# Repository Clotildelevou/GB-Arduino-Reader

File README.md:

# GB-Arduino-Reader
This is a little PCB connecting an arduino to a GBA cardtrige connector. The final aim of this project is to dump the cartdrige's ROM and enevtually write on the RAM. 

# Progress

**Hardware :**

▰▰▰▰▰▰▰▰▰▰ 100%
> The PCB first version exists and is functionnal. A wild second version may appear !

**Microcontroller's code :**

▰▱▱▱▱▱▱▱▱▱ 10%
> A POC exists and it is actually possible to fetch some code !

**Executor code :**

▰▰▰▰▰▰▰▰▰▱ 90%
> The ROM dumper is ready ! Different types of MBC are not supported yet tho

# Principles

## The Cartdridge

The cartdrige has 32 pins and this is their usage :

| Pin | Name    | Description        |
|-----|---------|--------------------|
| 1   | VCC     | +5VDC              |
| 2   | PHI     | CPU Clock          |
| 3   | WR      | Write              |
| 4   | RD      | Read               |
| 5   | CS      | SRAM select        |
| 6   | A0      | Address 0          |
| 7   | A1      | Address 1          |
| 8   | A2      | Address 2          |
| 9   | A3      | Address 3          |
| 10  | A4      | Address 4          |
| 11  | A5      | Address 5          |
| 12  | A6      | Address 6          |
| 13  | A7      | Address 7          |
| 14  | A8      | Address 8          |
| 15  | A9      | Address 9          |
| 16  | A10     | Address 10         |
| 17  | A11     | Address 11         |
| 18  | A12     | Address 12         |
| 19  | A13     | Address 13         |
| 20  | A14     | Address 14         |
| 21  | A15     | Address 15         |
| 22  | D0      | Data 0             |
| 23  | D1      | Data 1             |
| 24  | D2      | Data 2             |
| 25  | D3      | Data 3             |
| 26  | D4      | Data 4             |
| 27  | D5      | Data 5             |
| 28  | D6      | Data 6             |
| 29  | D7      | Data 7             |
| 30  | RST     | Reset              |
| 31  | AUDIOIN | Used by MP3 player |
| 32  | GND     | Ground             |

## The Shift Registers

The arduino we use (Arduino Nano V3.X) only has 22 digital pins. Shift registers become handy. Shift registers are often used for the purpose of saving pins on the microcontroller, as every microcontroller has a limited number of I/O pins (GPIO).

### The logic
The 595 has two registers (which can be thought of as “memory containers”), each with just 8 bits of data. The first one is called the Shift Register. The Shift Register lies deep within the IC circuits, quietly accepting input.

Whenever we apply a clock pulse to a 595, two things happen:

The bits in the Shift Register move one step to the left. For example, Bit 7 accepts the value that was previously in bit 6, bit 6 gets the value of bit 5 etc.
Bit 0 in the Shift Register accepts the current value on DATA pin. At the rising edge of the pulse, if the data pin is high, then a 1 gets pushed into the shift register. Otherwise, it is a 0.
On enabling the Latch pin, the contents of Shift Register are copied into the second register, called the Storage/Latch Register. Each bit of the Storage Register is connected to one of the output pins QA–QH of the IC, so in general, when the value in the Storage Register changes, so do the outputs.

### Pinout

**GND** should be connected to the ground of Arduino.

**VCC** is the power supply for 74HC595 shift register which we connect the 5V pin on the Arduino.

**SER** (Serial Input) pin is used to feed data into the shift register a bit at a time.

**SRCLK** (Shift Register Clock) is the clock for the shift register. The 595 is clock-driven on the rising edge. This means that in order to shift bits into the shift register, the clock must be HIGH. And bits are transferred in on the rising edge of the clock.

**RCLK** (Register Clock / Latch) is a very important pin. When driven HIGH, the contents of Shift Register are copied into the Storage/Latch Register; which ultimately shows up at the output. So the latch pin can be seen as like the final step in the process to seeing our results at the output, which in this case are LEDs.

**SRCLR** (Shift Register Clear) pin allows us to reset the entire Shift Register, making all its bits 0, at once. This is a negative logic pin, so to perform this reset; we need to set the SRCLR pin LOW. When no reset is required, this pin should be HIGH.

**OE** (Output Enable) is negative logic too: When the voltage on it is HIGH, the output pins are disabled/set to high impedance state and don’t allow current to flow. When OE gets low voltage, the output pins work normally.

**QA–QH** (Output Enable) are the output pins and should be connected to some type of output like LEDs, 7 Segments etc.

**QH’** Pin outputs bit 7 of the ShiftRegister. It is there so that we may daisychain 595s: if you connect this QH’ to the SER pin of another 595, and give both ICs the same clock signal, they will behave like a single IC with 16 outputs. Of course, this technique is not limited to two ICs – you can daisychain as many as you like, if you have enough power for all of them.

# 3D View
This is currently the result of my work : 

# Gerber view
This is the gerber view :

# Result

## Pictures
The PCB i got looks like this :

## Problems on the PCB

I had a little problem on the card. The GBA pads were a bit hidden the pins of the cartdrigde reader. To solve this problem I just removed the little plastic guides (see image below) with a plier and i glued it directly on the PCB. It is quite solid but i'll change the guides position for the next version !

# Sources
[Inside Gadgets](https://www.insidegadgets.com)

[lastminuteengineers](https://lastminuteengineers.com/74hc595-shift-register-arduino-tutorial/)

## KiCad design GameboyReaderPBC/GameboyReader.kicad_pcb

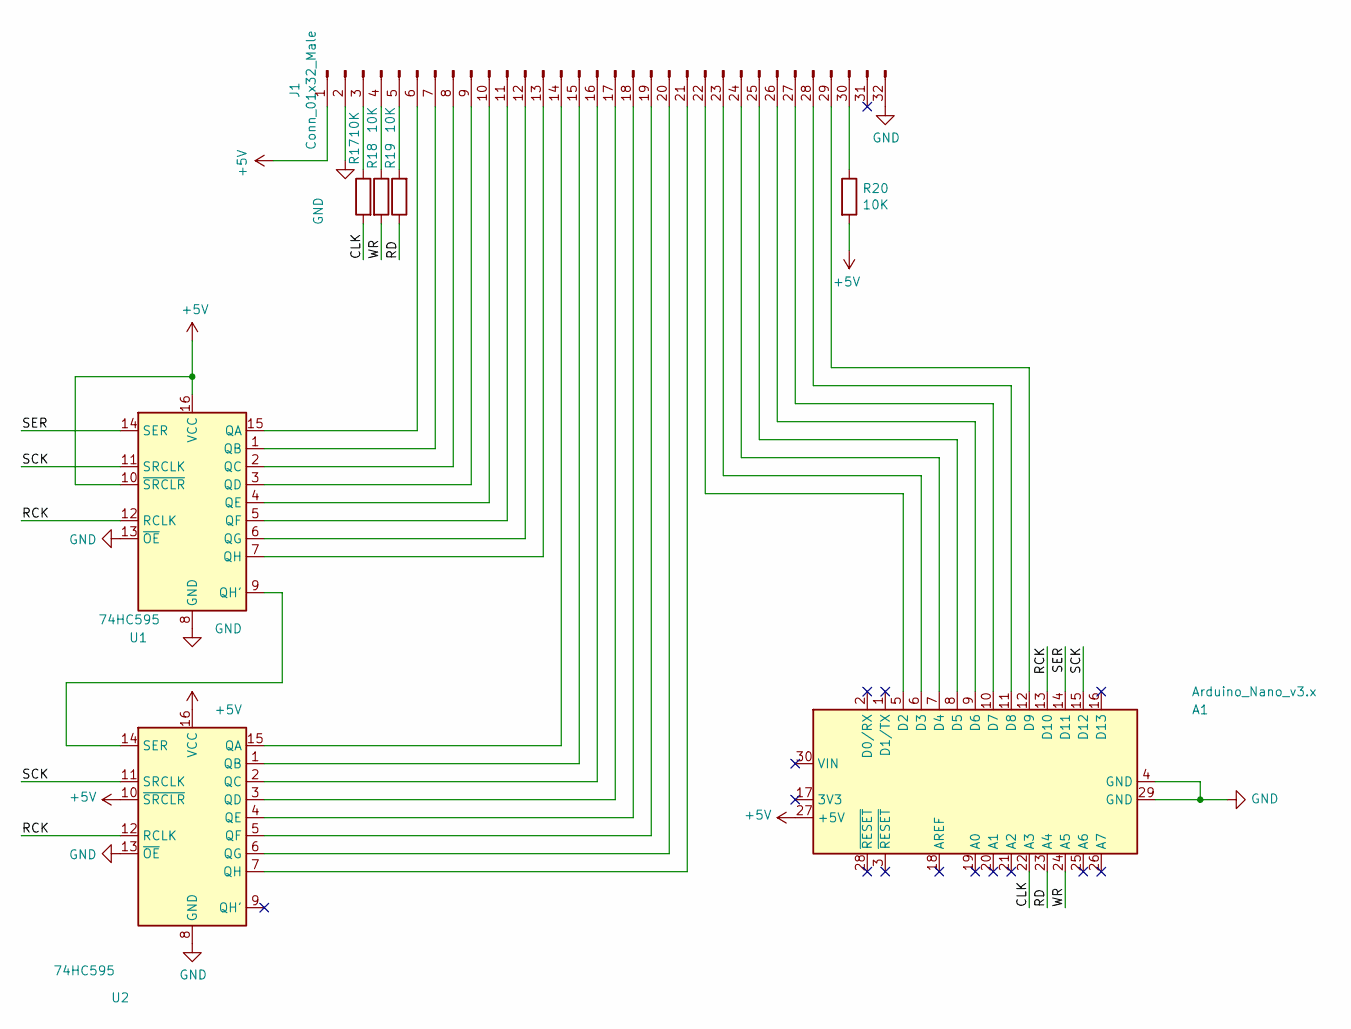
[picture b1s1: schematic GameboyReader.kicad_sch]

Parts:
A1: Arduino_Nano_v3.x; Arduino_Nano
J1: Conn_01x32_Male; GameboyConnector
R17, R18, R19, R20: 10K; R_0603_1608Metric
U1, U2: 74HC595; DIP-16_W10.16mm

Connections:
+5V: A1.27 (+5V), J1.1, R20.2, U1.10 (~SRCLR), U1.16 (VCC), U2.10 (~SRCLR), U2.16 (VCC)
/CLK: A1.22 (A3), R17.2
/RCK: A1.13 (D10), U1.12 (RCLK), U2.12 (RCLK)
/RD: A1.23 (A4), R19.1
/SCK: A1.15 (D12), U1.11 (SRCLK), U2.11 (SRCLK)
/SER: A1.14 (D11), U1.14 (SER)
/WR: A1.24 (A5), R18.2
GND: A1.4 (GND), A1.29 (GND), J1.2, J1.32, U1.8 (GND), U1.13 (~OE), U2.8 (GND), U2.13 (~OE)
unnamed: A1.5 (D2), J1.22
unnamed: A1.6 (D3), J1.23
unnamed: A1.7 (D4), J1.24
unnamed: A1.8 (D5), J1.25
unnamed: A1.9 (D6), J1.26
unnamed: A1.10 (D7), J1.27
unnamed: A1.11 (D8), J1.28
unnamed: A1.12 (D9), J1.29
unnamed: J1.3, R17.1
unnamed: J1.4, R18.1
unnamed: J1.5, R19.2
unnamed: J1.6, U1.15 (QA)
unnamed: J1.7, U1.1 (QB)
unnamed: J1.8, U1.2 (QC)
unnamed: J1.9, U1.3 (QD)
unnamed: J1.10, U1.4 (QE)
unnamed: J1.11, U1.5 (QF)
unnamed: J1.12, U1.6 (QG)
unnamed: J1.13, U1.7 (QH)
unnamed: J1.14, U2.15 (QA)
unnamed: J1.15, U2.1 (QB)
unnamed: J1.16, U2.2 (QC)
unnamed: J1.17, U2.3 (QD)
unnamed: J1.18, U2.4 (QE)
unnamed: J1.19, U2.5 (QF)
unnamed: J1.20, U2.6 (QG)
unnamed: J1.21, U2.7 (QH)
unnamed: J1.30, R20.1
unnamed: U1.9 (QH'), U2.14 (SER)

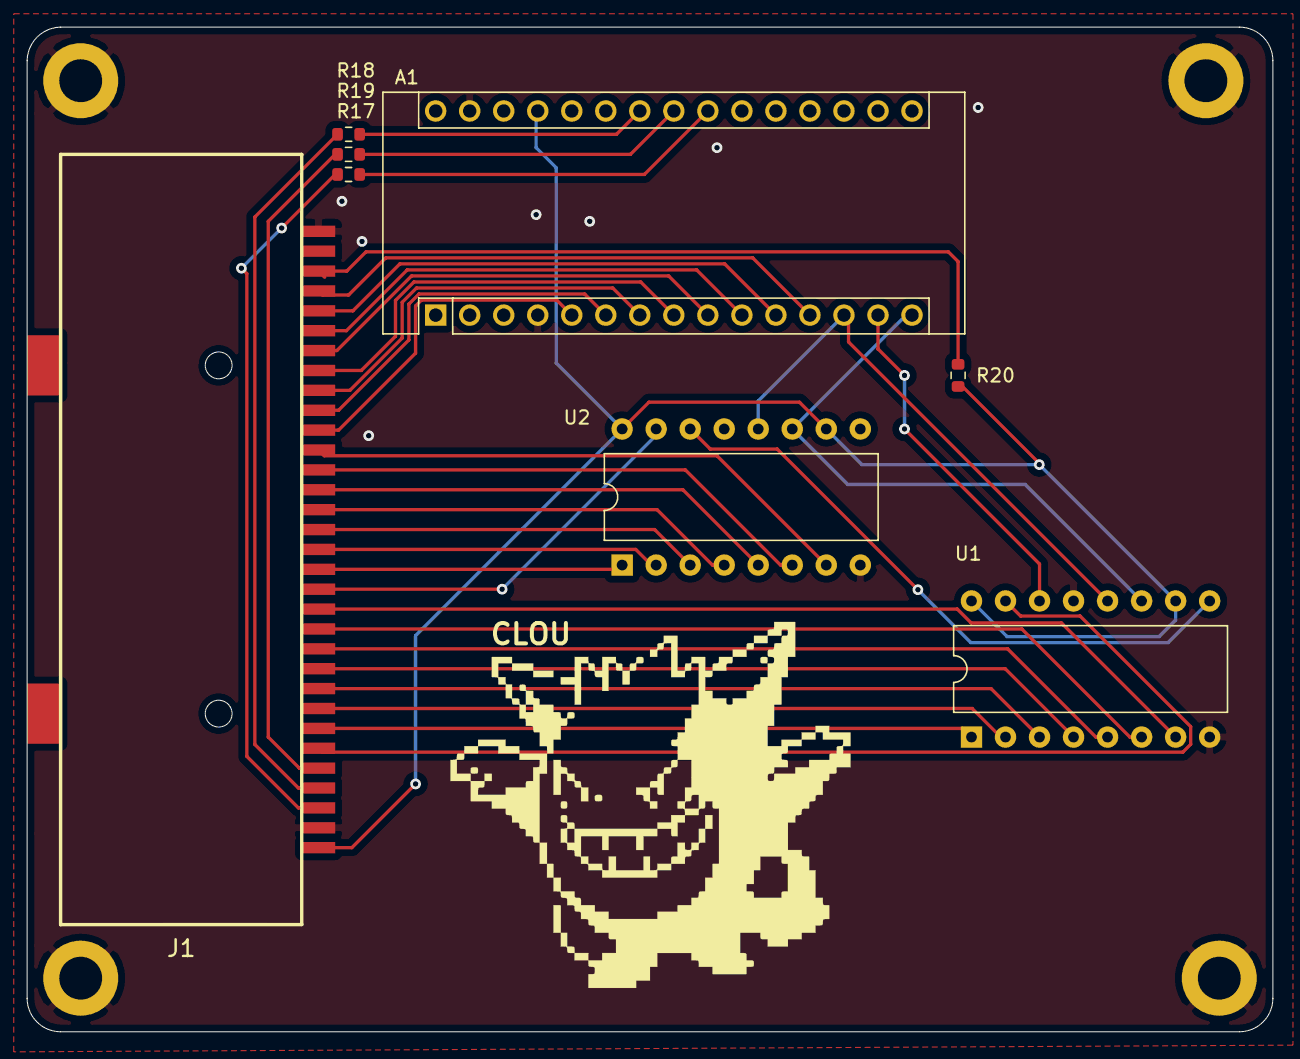
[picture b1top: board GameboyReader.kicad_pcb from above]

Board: 2 copper layers, 93.0 x 75.0 mm, 8 parts (0 on the bottom side), 37 nets.

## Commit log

2021-10-24 [IMG] 3d view card
2021-10-24 [ARCH] gitignore
2021-10-24 [PROJECT] Project done :)
2021-10-24 [IMG] Gerber view
2021-10-29 [FIX] Regenerated gerbers
2021-10-29 [IMG] Added images
2021-11-12 [IMG] Real card
2021-11-17 [REFACTO] dirname
2021-11-17 [FEAT][WIP] RS232 Protocol header
2021-11-17 [FIX] Updated gitignore
2021-11-17 [FEAT] Soldered Picture
2021-11-17 [IMG] Pic card reader
2021-11-18 [FEAT] open serial connection
2021-11-18 [FIX] Removed old protocol
2021-11-18 [FEAT] Basic makefile
2021-11-18 [FIX] Print error
2021-11-18 [FEAT] Write function
2021-11-18 [FIX] useless fct removal
2021-11-18 [FIX] Baudrate removal
2021-11-18 [FIX] Serial.h define
2021-11-18 [FIX] string print
2021-11-18 [FEAT] read functions
2021-11-18 [FEAT] Flush func
2022-10-08 arch: updated media
2022-10-10 uart: first commit
2022-10-10 kicad: updated versions extensions
2022-10-10 gitignore : zip
2022-10-10 uart: uart init
2022-10-12 uart: init with interruptions
2022-10-12 uart: send bytes
2022-10-12 uart: send buffer
2022-10-12 uart: first test
2022-10-12 uart: makefile
2022-10-12 uart fix: baudrate formula
2022-10-12 uart fix: interrupts enabled
2022-10-12 makefile: flash properties
2022-10-12 gitignore
2022-10-12 uart: send string
2022-10-17 uart: interrupt handler moved
2022-10-17 uart: tx functions reordered
2022-10-17 uart: rx interrupt handler
2022-10-17 uart: rx byte
2022-10-17 uart: rx buffer
